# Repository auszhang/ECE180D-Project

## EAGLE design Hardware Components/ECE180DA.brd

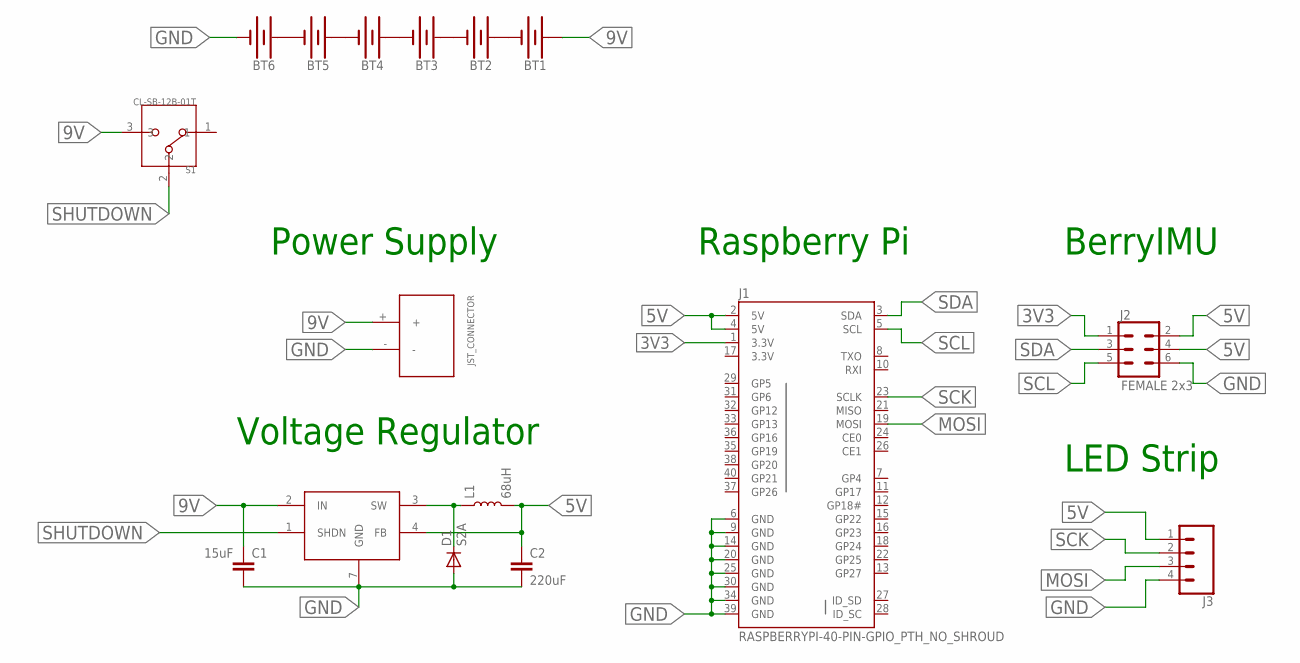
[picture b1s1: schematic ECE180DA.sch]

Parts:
BT1, BT2, BT3, BT4, BT5, BT6: BATTERY-AA
C1: 15uF; C0603K
C2: 220uF; C1206K
D1: S2A; DO214AA
J1: RASPBERRYPI-40-PIN-GPIO_PTH_NO_SHROUD; 2X20
J2: FEMALE 2x3; 2X3
J3: CONN_04; 1X04
L1: 68uH; 0603
S1: CL-SB-12B-01T; CL-SB-12B
U$1: MIC4680; SOIC-8
U$3: JST_CONNECTOR_FEMALE

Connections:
3V3: J1.1 (3.3V), J1.17 (3.3V), J2.1
5V: C2.1, J1.2 (5V), J1.4 (5V), J2.2, J2.4, J3.1, L1.2, U$1.4 (FB)
9V: BT1.PWR@1 (+), C1.1, S1.3, U$1.2 (IN), U$3.+
GND: BT6.GND@1 (-), C1.2, C2.2, D1.A, J1.6 (GND), J1.9 (GND), J1.14 (GND), J1.20 (GND), J1.25 (GND), J1.30 (GND), J1.34 (GND), J1.39 (GND), J2.6, J3.4, U$1.5 (GND), U$1.6 (GND), U$1.7 (GND), U$1.8 (GND), U$3.-
MOSI: J1.19 (MOSI), J3.3
unnamed: BT1.GND@1 (-), BT2.PWR@1 (+)
unnamed: BT2.GND@1 (-), BT3.PWR@1 (+)
unnamed: BT3.GND@1 (-), BT4.PWR@1 (+)
unnamed: BT4.GND@1 (-), BT5.PWR@1 (+)
unnamed: BT5.GND@1 (-), BT6.PWR@1 (+)
unnamed: D1.C, L1.1, U$1.3 (SW)
SCK: J1.23 (SCLK), J3.2
SCL: J1.5 (SCL), J2.5
SDA: J1.3 (SDA), J2.3
SHUTDOWN: S1.2, U$1.1 (SHDN)

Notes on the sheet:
Power Supply
Voltage Regulator
Raspberry Pi
BerryIMU
LED Strip

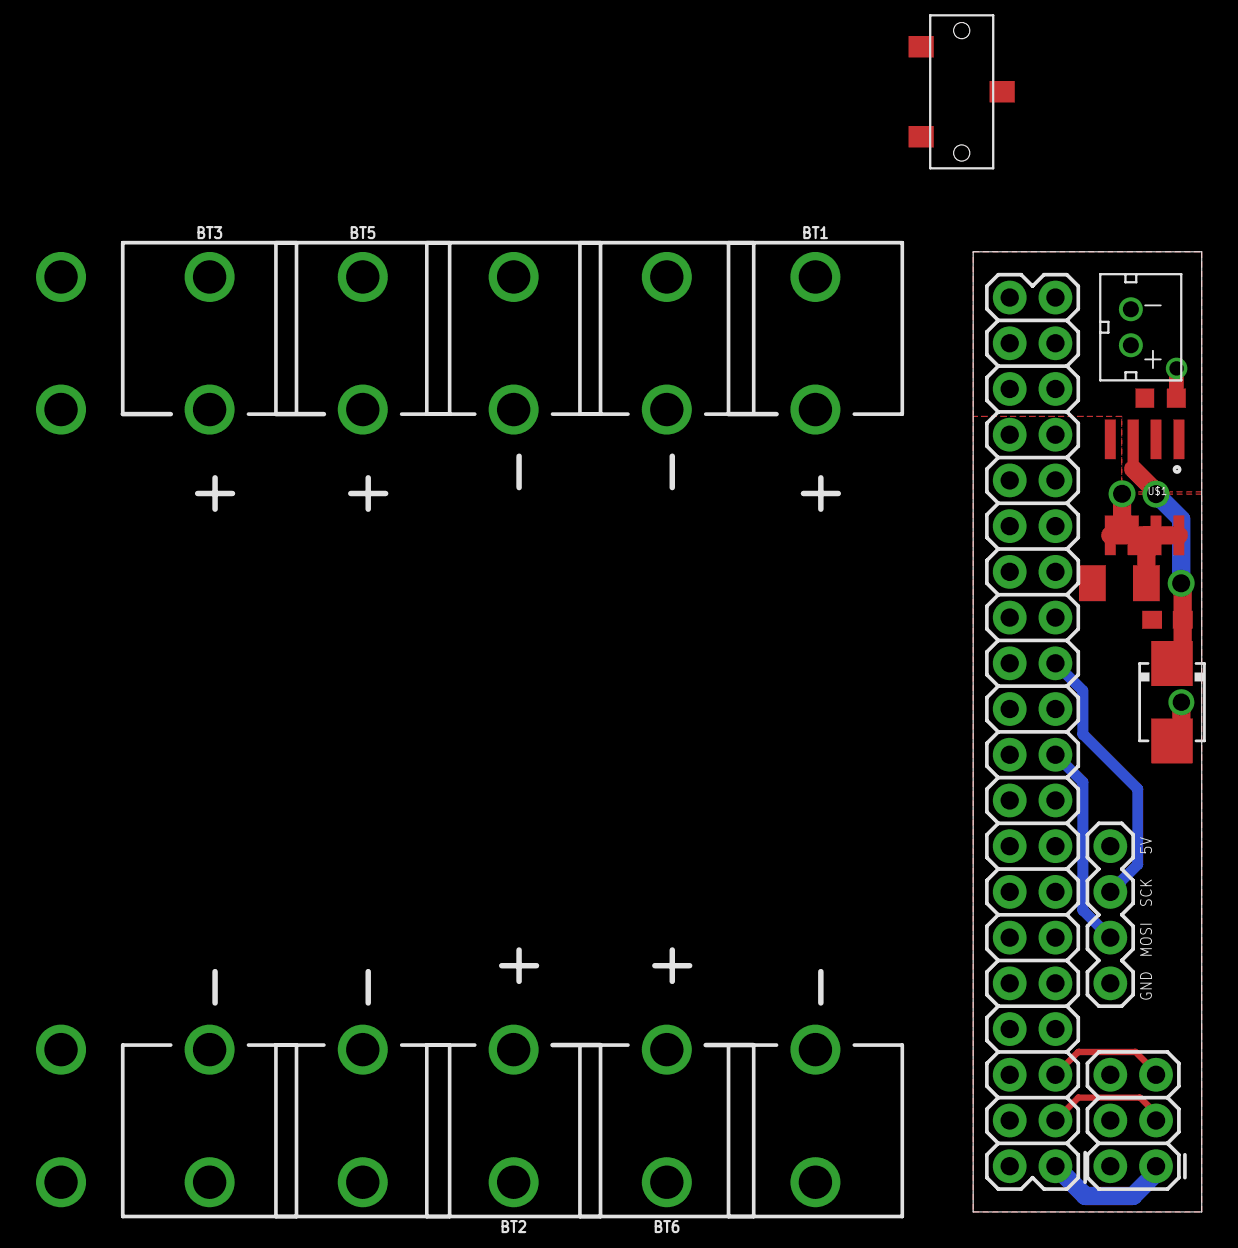
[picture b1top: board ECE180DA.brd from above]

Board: 2 copper layers, 12.7 x 53.3 mm, 16 parts (1 on the bottom side), 15 nets.

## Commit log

2019-11-05 Add files via upload
    Localization function
2019-11-08 initialized mobile app
2019-11-08 Revert "initialized mobile app"
    This reverts commit aa5462b3ecc083fb2631579a4affb7eccd2c2a0f.
2019-11-08 clean install
2019-11-08 started working on bluetooth api
2019-11-08 added dummy form
2019-11-10 add windows MQTT file
2019-11-10 MQTT Raspberry Pi code
2019-11-13 added new activity for sent position
2019-11-13 cleaned up UI and added new activity for bluetooth setup
2019-11-13 using mqtt make LED light up
2019-11-13 built buttons that turn bluetooth on/off, makes phone discoverable
2019-11-14 Both server and client publish and receive
2019-11-14 Added findMaxFullGrid function
2019-11-14 fixed button alignment
2019-11-14 Add server-side localization/lighting helpers
2019-11-14 merged on and off buttons into toggle button, added discover feature
2019-11-14 displays list of available devices
2019-11-14 implemented bluetooth device pairing
2019-11-14 cleaned up server/client side with LED assignments
2019-11-15 added conditionals to check for API sensitive permission calls
2019-11-15 cleaned up code and removed unused imports
2019-11-15 added project spec
2019-11-15 Accept user name from command line, hash for client id
2019-11-15 Add client name to payload
2019-11-15 Adding in IMU sample code
2019-11-15 Adding hardware designs
2019-11-15 added server socket handling on separate thread
2019-11-15 More IMU code
2019-11-15 added minor LED function
2019-11-18 better comments
2019-11-20 added server and client thread functions
2019-11-20 added functions that initiate server/client threads, fixed broken connected method
2019-11-20 can now write/read input streams
2019-11-20 added default constructor to fix crashes
2019-11-20 changed text input to hint, commit before i mess things up lol
2019-11-20 fixed more crashing due to unregisterReceiver method - LAST WORKING VERSION
2019-11-21 Reading Magnetometer
2019-11-21 can now send message to paired pi over bluetooth IT WORKS YAY
2019-11-21 added raspberry pi rfcomm script
2019-11-22 added raspberry pi get bluetooth working instructions
2019-11-22 Add Bluetooth to MQTT client
2019-12-01 Added UCLA lighting scheme
2019-12-04 Serene added enact lights basic function
2019-12-05 Added lighting schemes to server + client
2019-12-05 Fixed client side bugs for lighting
2019-12-05 now handles different device names
2019-12-05 Last will to handle ungraceful client disconnection
2019-12-05 Prioritize most recently received client data
2019-12-06 12-5
2019-12-06 ui cleanup part 1
2019-12-06 debugging in lab 12/5
2019-12-06 ui cleanup part 2 - first coach mark
2019-12-06 ui cleanup 3 - added coach mark for bt
2019-12-06 Fixed last will for disgraceful client disconnect
2019-12-06 accounted for lighting sequence 3 clients
2019-12-06 ui cleanup done
2019-12-07 Change server array of client data to hash table
2019-12-07 Working IMU code added
2019-12-08 added colors to lighting sequences
2019-12-08 Adding Bill of Materials
2019-12-08 Adding Bill or Materials
2019-12-08 Copied client to integrate with IMU compass
2019-12-08 Importing IMU code to client code
2019-12-08 Setting up IMU_Code Folder
2019-12-08 Working compass in client
2019-12-08 Incorporate IMU with lighting
2019-12-08 Calibration data stored locally
2019-12-09 Implemented get_rotation helper
2019-12-09 Minor debugging of print statements
2019-12-09 Fixed rotation function
2019-12-09 fixed IMU frequency reading
2020-01-28 Move grad cap work into Fall folder, create Winter folder
2020-01-28 Copy MQTT code
2020-01-28 Server for tracking game state
2020-01-29 minor lighting helpers change
2020-01-29 Add client side game logic
2020-01-29 jan29 serene
2020-01-29 Initial hotpotato Test Results
2020-01-29 Start work for fixing publish
2020-02-05 Starting Gesture Recognition
2020-02-05 Adding motion tracking code and graphs
2020-02-05 Client/server continually publish over MQTT
2020-02-05 Established basic hot potato workflow
2020-02-05 Server update
2020-02-06 Super simple gesture recognition
2020-02-09 changed speech rec dictionary
2020-02-09 Allow server to delete clients from game
2020-02-09 added alternate pronunciation with across
2020-02-09 Converting gesture rec for client.py
2020-02-09 Fix server bug
2020-02-09 Reset game if client holding potato dies
2020-02-09 Integrated gesture recognition
2020-02-10 Added lights for hot potato
2020-02-11 Included alternate gesture recognition file
2020-02-11 Included hot / cold color schemes :
2020-02-11 Cleaning up IMU_Code
2020-02-11 IMU graphing for Michelle's RPi
2020-02-11 Adding Serene graph
2020-02-11 Adding Austin Graph
2020-02-11 Renamed files
2020-02-12 Rainbow lights
2020-02-12 Minor color change
2020-02-17 Added timer functionality to client
2020-02-17 Added OUTOFTIME msg
2020-02-19 Implemented corresponding lighting for timer sequence
2020-02-19 added livespeech parameters to server
2020-02-19 Added timer to server
2020-02-23 Adding PWM to client1
2020-02-25 integrated speech recognition -austin
2020-02-26 fixed some stuff
2020-02-26 Added Google Cloud speech recognition test
2020-02-26 Added client temp
2020-02-27 testing speech stuff
2020-02-27 changed last_phrase to global
2020-02-27 Adding vib motor
2020-02-27 Adding offset calculation
2020-02-29 2 new gesture recs
2020-02-29 Fix TestingDistance
2020-02-29 Fix valid move bug
2020-02-29 Adding Distance to client1
2020-02-29 Prepping to multithread client
2020-02-29 Gesture Recognition thread set up
2020-02-29 Remove .csv files
2020-03-01 Fixed filters
2020-03-01 THIS BITCH READY
2020-03-02 Preping for B I G F I L T E R
2020-03-02 Oh god it's in it's in
2020-03-02 Pre-testing client
2020-03-03 Removing unnecessary stuff
2020-03-03 Added USE_CMD_LINE boolean
2020-03-03 Client integrated correctly
2020-03-03 Fix my heading daddy
2020-03-03 removed random app folder, slightly modified app
2020-03-03 Added Bluetooth successfully
2020-03-03 Added win condition
2020-03-04 Minor server changes
2020-03-04 Added winning sequence
2020-03-04 Added lights + vibration adjustment
2020-03-04 Fixed fail pass bug
2020-03-05 Gesture my position
2020-03-05 flipper added
2020-03-09 Fix?
2020-03-10 improved speech rec
2020-05-23 Added TF version of gesture recognition
2020-05-27 TF done

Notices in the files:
parts and their libraries:
SparkFun-Connectors: Licensing: Creative Commons ShareAlike 4.0 International - https://creativecommons.org/licenses/by-sa/4.0
